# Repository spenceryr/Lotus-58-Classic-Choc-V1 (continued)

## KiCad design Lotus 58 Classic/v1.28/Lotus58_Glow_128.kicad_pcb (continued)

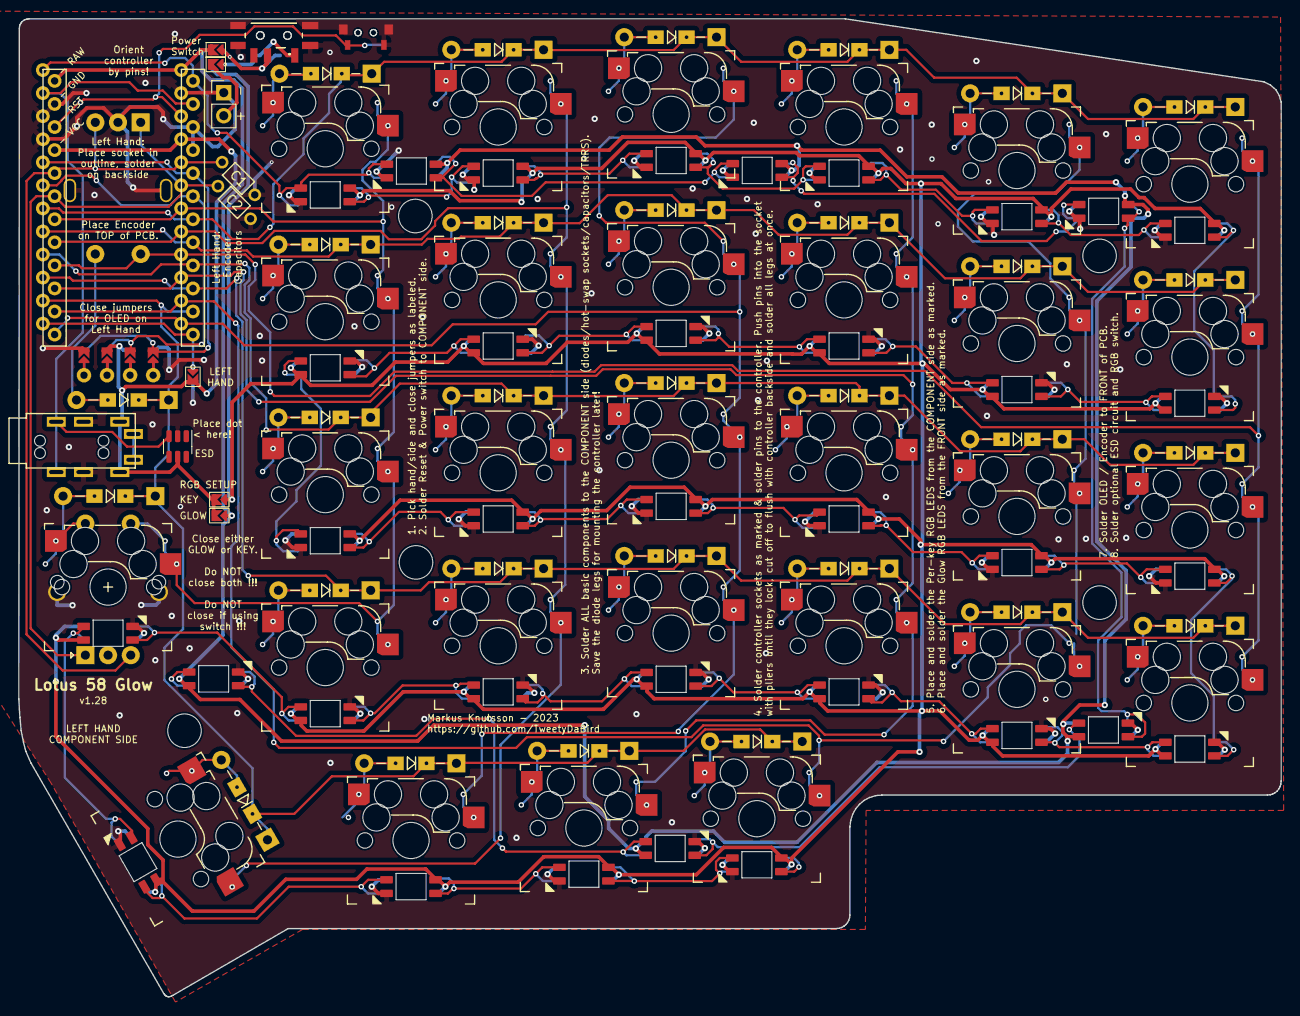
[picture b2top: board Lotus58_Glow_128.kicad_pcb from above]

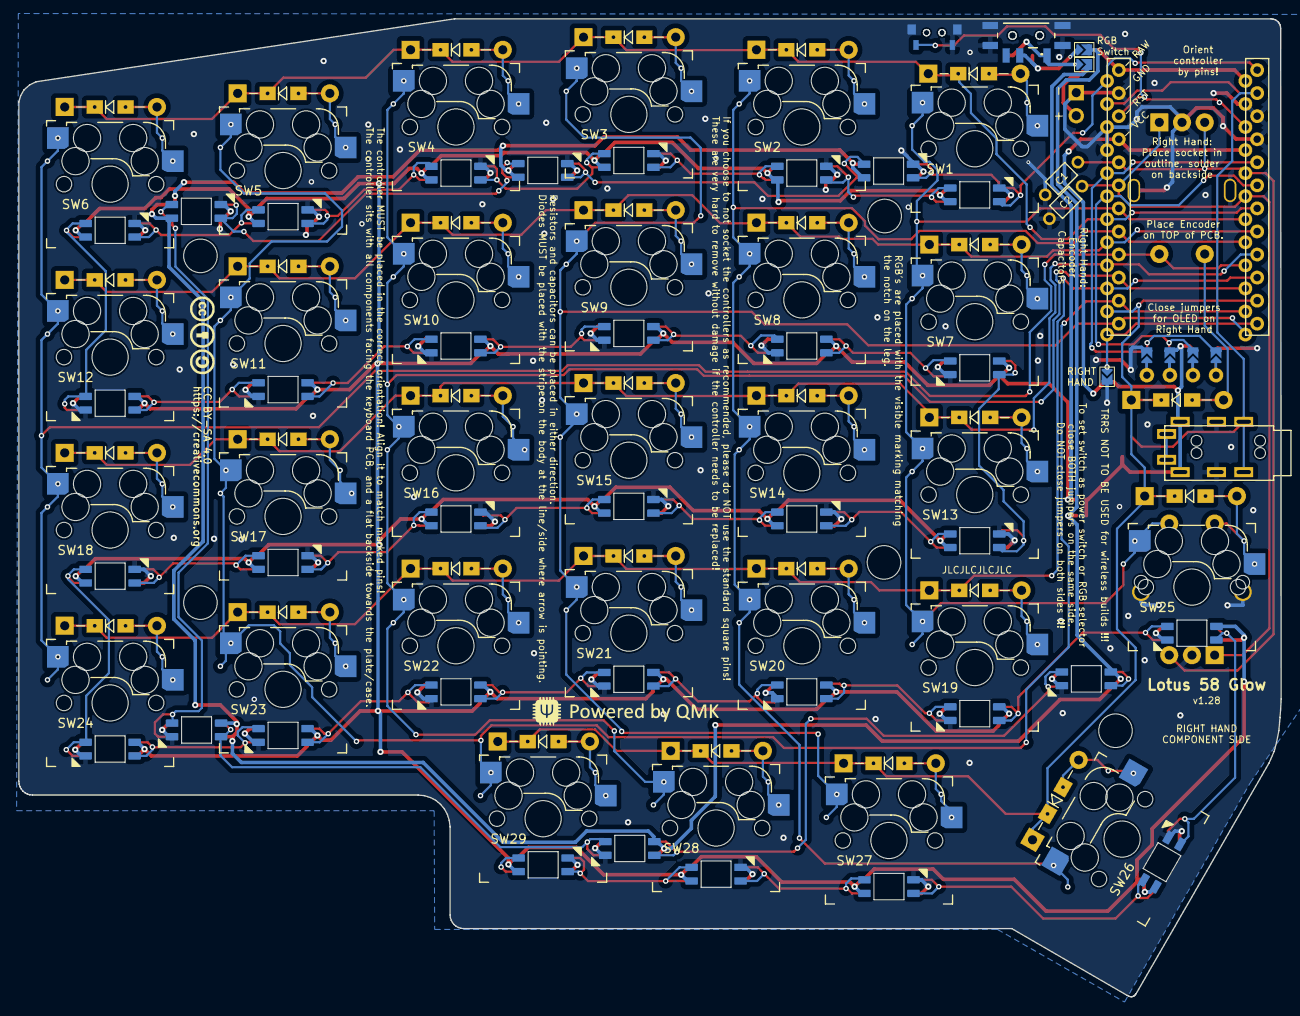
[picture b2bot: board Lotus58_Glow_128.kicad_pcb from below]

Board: 2 copper layers, 139.1 x 107.7 mm, 122 parts (73 on the bottom side), 90 nets.

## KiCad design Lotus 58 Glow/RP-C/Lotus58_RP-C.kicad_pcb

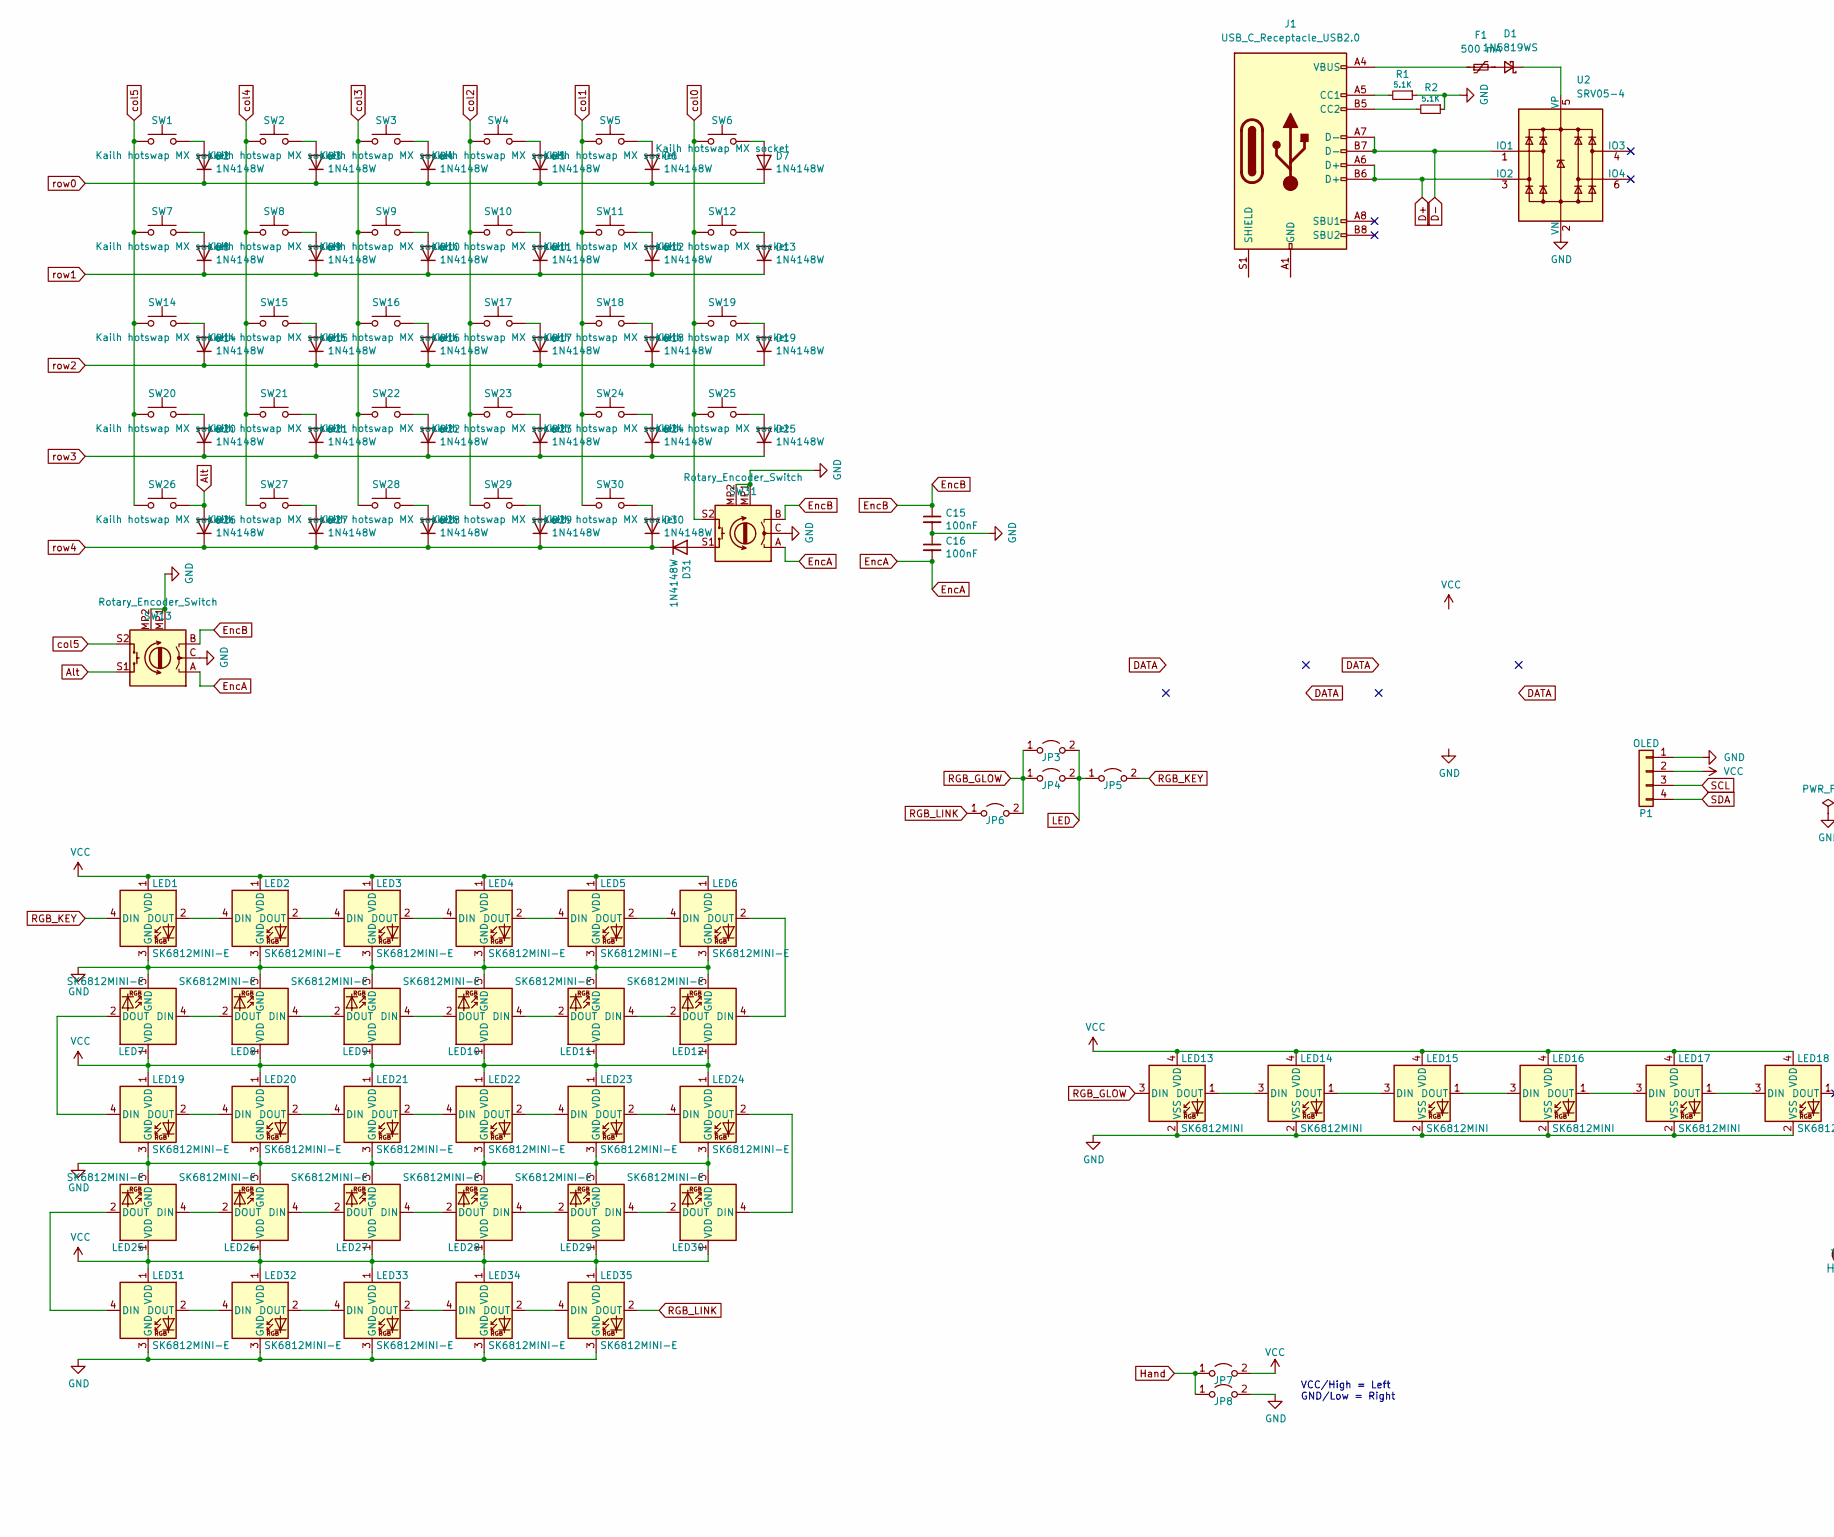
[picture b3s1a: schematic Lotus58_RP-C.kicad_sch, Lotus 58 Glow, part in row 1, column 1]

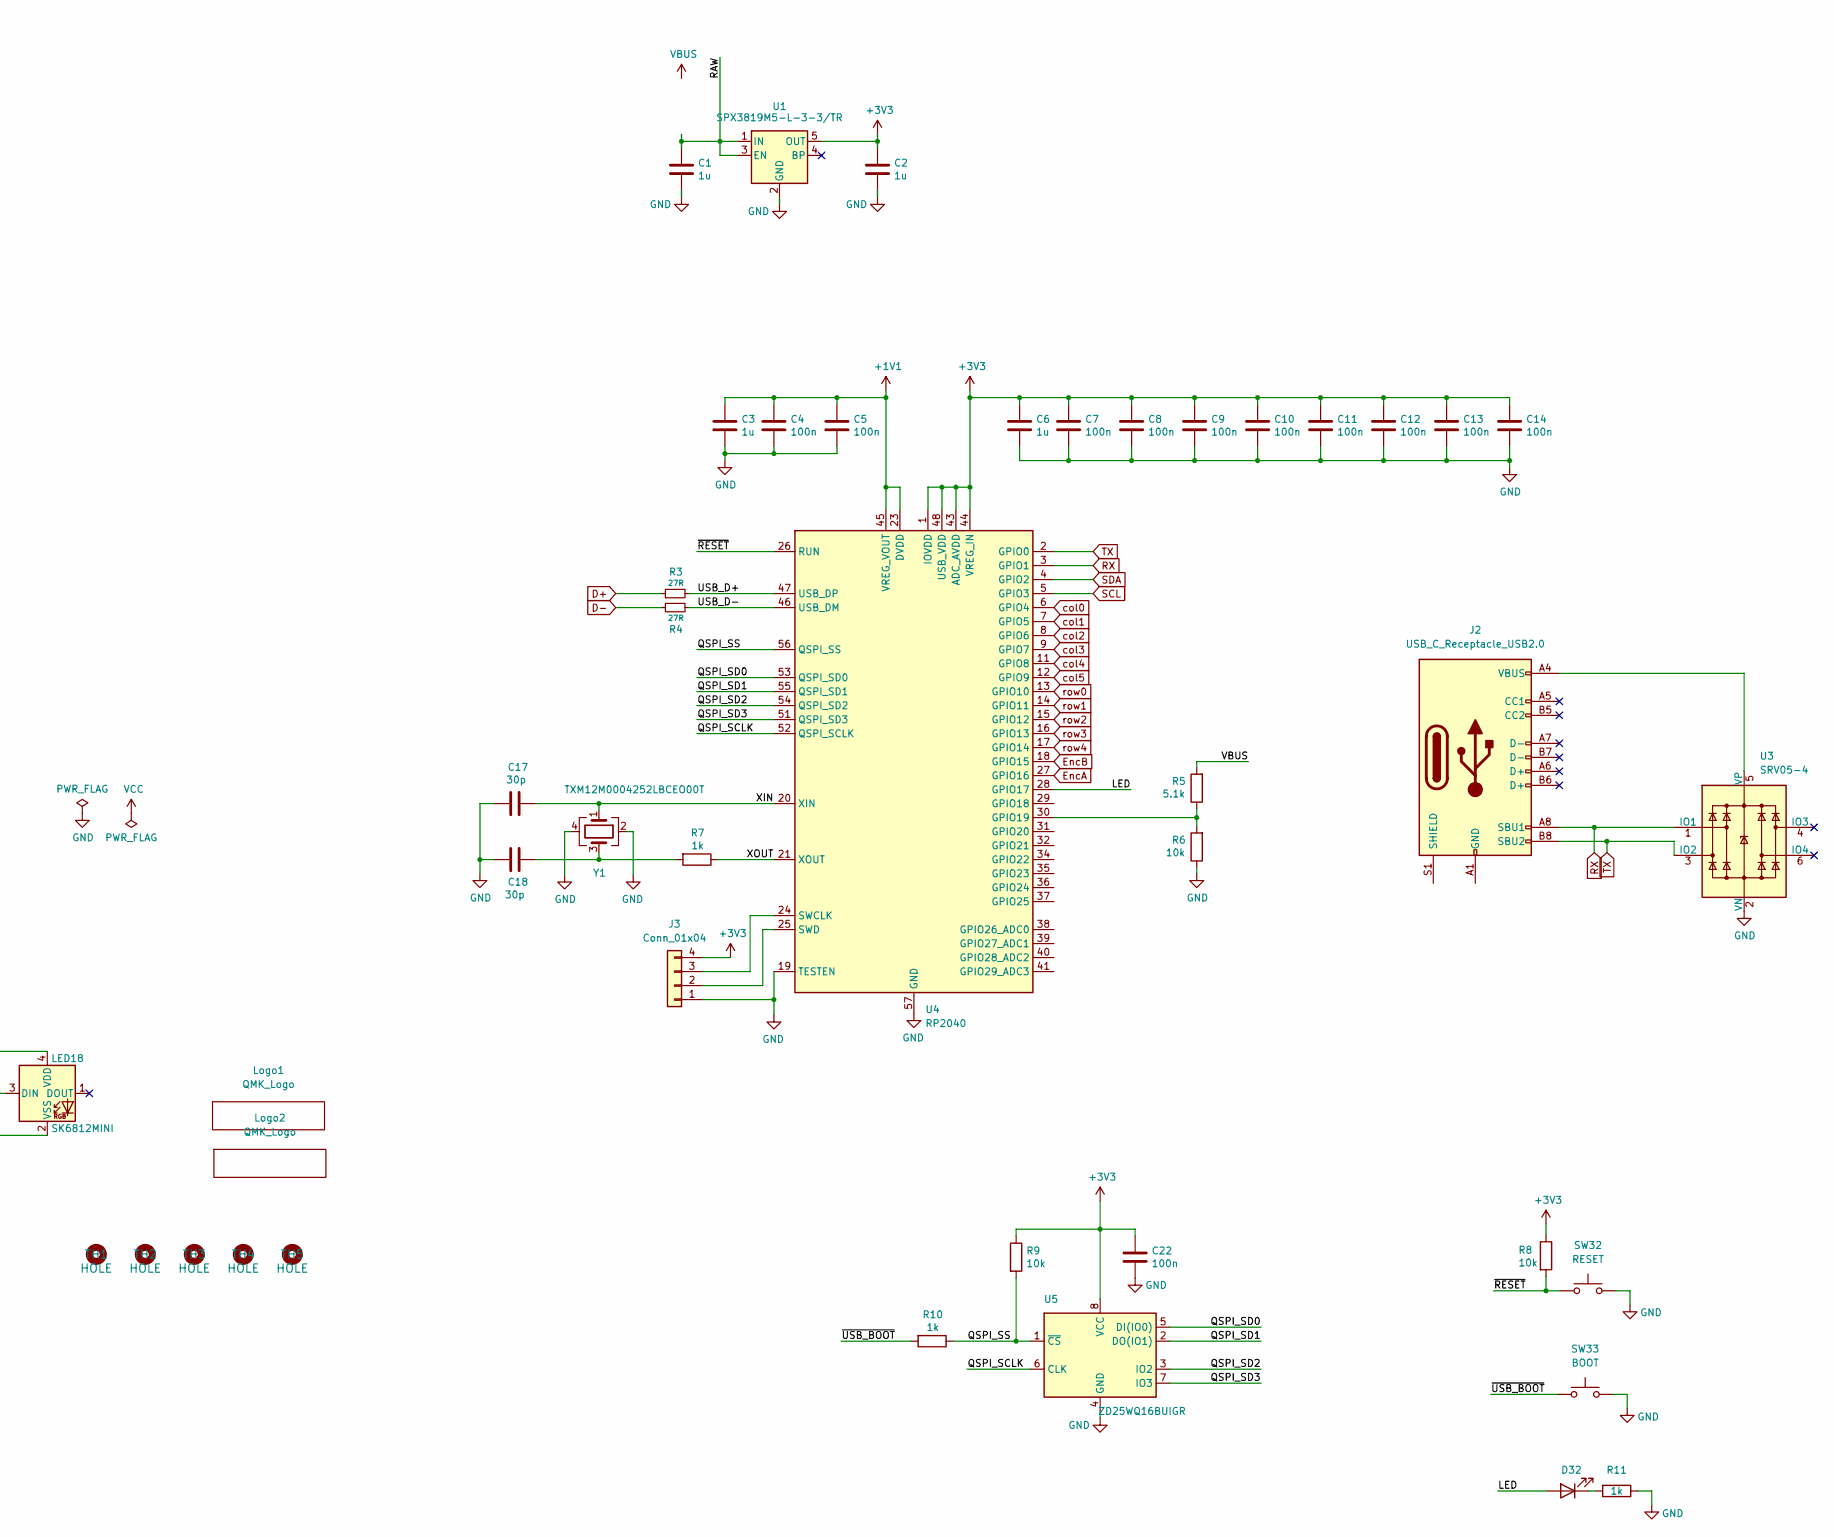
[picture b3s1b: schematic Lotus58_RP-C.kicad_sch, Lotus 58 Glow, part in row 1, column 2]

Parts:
C1, C2, C3, C6: 1u; C_0402_1005Metric
C4, C5, C7, C8, C9, C10, C11, C12, C13, C14, C22: 100n; C_0402_1005Metric
C15, C16: 100nF; RESISTOR_Reversible
C17, C18: 30p; C_0402_1005Metric
D1: 1N5819WS; D_SOD-323F
D2, D3, D4, D5, D6, D7, D8, D9, D10, D11, D12, D13, D14, D15, D16, D17, D18, D19, D20, D21, D22, D23, D24, D25, D26, D27, D28, D29, D30, D31: 1N4148W; D_SOD-123
D32: LED; LED_0402_1005Metric; LCSC C130719
F1: 500 mA; R_0805_2012Metric
J1, J2: USB_C_Receptacle_USB2.0; GT-USB-7014C
J3: Conn_01x04; PinHeader_1x04_P2.00mm_Vertical
JP3, JP4, JP5, JP6: FULL; Jumper_Mini
JP7: LEFT; Jumper_Mini
JP8: RIGHT; Jumper_Mini
LED1, LED2, LED3, LED4, LED5, LED6, LED7, LED8, LED9, LED10, LED11, LED12, LED19, LED20, LED21, LED22, LED23, LED24, LED25, LED26, LED27, LED28, LED29, LED30, LED31, LED32, LED33, LED34, LED35: SK6812MINI-E; MX_SK6812MINI-E_REVERSIBLE
LED13, LED14, LED15, LED16, LED17, LED18: SK6812MINI; LED_SK6812MINI_PLCC4_3.5x3.5mm_P1.75mmdouble
Logo1, Logo2: QMK_Logo; qmk logo
P1: OLED; SSD1306-0.91-OLED-4pin-128x32 doublesided
R1, R2: 5.1K; R_0402_1005Metric
R3, R4: 27R; R_0402_1005Metric
R5: 5.1k; R_0402_1005Metric
R6, R8, R9: 10k; R_0402_1005Metric
R7, R10: 1k; R_0402_1005Metric
R11: 1k; R_0402_1005Metric; LCSC C11702
SW1, SW2, SW3, SW4, SW5, SW6, SW7, SW8, SW9, SW10, SW11, SW12, SW14, SW15, SW16, SW17, SW18, SW19, SW20, SW21, SW22, SW23, SW24, SW25, SW26, SW27, SW28, SW29, SW30: Kailh hotswap MX socket; SW_MX_HotSwap_Reversible
SW13: Rotary_Encoder_Switch; Encoder_Alps_EC11E_Offset_pad
SW31: Rotary_Encoder_Switch; Encoder_Alps_EC11E_Small
SW32: RESET; YTS-A002
SW33: BOOT; YTS-A002
TH1, TH2, TH3, TH4, TH5: HOLE; Spacer PCB hole
U1: SPX3819M5-L-3-3/TR; SOT-23-5
U2, U3: SRV05-4; SOT-23-6; LCSC C558418
U4: RP2040; QFN-56-1EP_7x7mm_P0.4mm_EP3.2x3.2mm
U5: ZD25WQ16BUIGR; DFN-8-1EP_3x2mm_P0.5mm_EP0.2x1.6mm; LCSC C2759920
Y1: TXM12M0004252LBCEO00T; Crystal_SMD_2520-4Pin_2.5x2.0mm; PartNo C284156

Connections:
+1V1: C3.1, C4.1, C5.1, U4.23 (DVDD), U4.45 (VREG_VOUT), U4.50 (DVDD)
+3V3: C2.1, C6.1, C7.1, C8.1, C9.1, C10.1, C11.1, C12.1, C13.1, C14.1, C22.1, J3.4, R8.1, R9.1, U1.5 (OUT), U4.1 (IOVDD), U4.10 (IOVDD), U4.22 (IOVDD), U4.33 (IOVDD), U4.42 (IOVDD), U4.43 (ADC_AVDD), U4.44 (VREG_IN), U4.48 (USB_VDD), U4.49 (IOVDD), U5.8 (VCC)
/QSPI_SCLK: U4.52 (QSPI_SCLK), U5.6 (CLK)
/QSPI_SD0: U4.53 (QSPI_SD0), U5.5 (DI(IO0))
/QSPI_SD1: U4.55 (QSPI_SD1), U5.2 (DO(IO1))
/QSPI_SD2: U4.54 (QSPI_SD2), U5.3 (IO2)
/QSPI_SD3: U4.51 (QSPI_SD3), U5.7 (IO3)
/QSPI_SS: R9.2, R10.1, U4.56 (QSPI_SS), U5.1 (~CS)
/RAW: C1.1, U1.1 (IN), U1.3 (EN)
/USB_D+: R3.2, U4.47 (USB_DP)
/USB_D-: R4.2, U4.46 (USB_DM)
/XIN: C17.1, U4.20 (XIN), Y1.1
/XOUT: R7.1, U4.21 (XOUT)
/~RESET: R8.2, SW32.1, U4.26 (RUN)
/~USB_BOOT: R10.2, SW33.1
Alt: D26.2 (A), SW13.S1, SW26.2
D+: J1.A6 (D+), J1.B6 (D+), R3.1, U2.3 (IO2)
D-: J1.A7 (D-), J1.B7 (D-), R4.1, U2.1 (IO1)
EncA: C16.2, SW13.A, SW31.A, U4.27 (GPIO16)
EncB: C15.1, SW13.B, SW31.B, U4.18 (GPIO15)
GND: C1.2, C2.2, C3.2, C4.2, C5.2, C6.2, C7.2, C8.2, C9.2, C10.2, C11.2, C12.2, C13.2, C14.2, C15.2, C16.1, C17.2, C18.2, C22.2, J3.1, JP8.2 (B), LED1.3 (GND), LED2.3 (GND), LED3.3 (GND), LED4.3 (GND), LED5.3 (GND), LED6.3 (GND), LED7.3 (GND), LED8.3 (GND), LED9.3 (GND), LED10.3 (GND), LED11.3 (GND), LED12.3 (GND), LED13.2 (VSS), LED14.2 (VSS), LED15.2 (VSS), LED16.2 (VSS), LED17.2 (VSS), LED18.2 (VSS), LED19.3 (GND), LED20.3 (GND), LED21.3 (GND), LED22.3 (GND), LED23.3 (GND), LED24.3 (GND), LED25.3 (GND), LED26.3 (GND), LED27.3 (GND), LED28.3 (GND), LED29.3 (GND), LED30.3 (GND), LED31.3 (GND), LED32.3 (GND), LED33.3 (GND), LED34.3 (GND), LED35.3 (GND), P1.1, R1.1, R2.1, R6.1, R11.1, SW13.C, SW13.MP1 (GND), SW13.MP2 (GND), SW31.C, SW31.MP1 (GND), SW31.MP2 (GND), SW32.2, SW33.2, U1.2 (GND), U2.2 (VN), U3.2 (VN), U4.19 (TESTEN), U4.57 (GND), U5.4 (GND), Y1.2, Y1.4
Hand: JP7.1 (A), JP8.1 (A)
LED: D32.2 (A), JP3.2 (B), JP4.2 (B), JP5.1 (A), U4.28 (GPIO17)
unnamed: C18.1, R7.2, Y1.3
unnamed: D1.1 (K), U2.5 (VP)
unnamed: D1.2 (A), F1.2
unnamed: D2.2 (A), SW1.1
unnamed: D3.2 (A), SW2.1
unnamed: D4.2 (A), SW3.1
unnamed: D5.2 (A), SW4.1
unnamed: D6.2 (A), SW5.1
unnamed: D7.2 (A), SW6.1
unnamed: D8.2 (A), SW7.1
unnamed: D9.2 (A), SW8.1
unnamed: D10.2 (A), SW9.1
unnamed: D11.2 (A), SW10.1
unnamed: D12.2 (A), SW11.1
unnamed: D13.2 (A), SW12.1
unnamed: D14.2 (A), SW14.1
unnamed: D15.2 (A), SW15.1
unnamed: D16.2 (A), SW16.1
unnamed: D17.2 (A), SW17.1
unnamed: D18.2 (A), SW18.1
unnamed: D19.2 (A), SW19.1
unnamed: D20.2 (A), SW20.1
unnamed: D21.2 (A), SW21.1
unnamed: D22.2 (A), SW22.1
unnamed: D23.2 (A), SW23.1
unnamed: D24.2 (A), SW24.1
unnamed: D25.2 (A), SW25.1
unnamed: D27.2 (A), SW27.1
unnamed: D28.2 (A), SW28.1
unnamed: D29.2 (A), SW29.1
unnamed: D30.2 (A), SW30.1
unnamed: D31.2 (A), SW31.S1
unnamed: D32.1 (K), R11.2
unnamed: F1.1, J1.A4 (VBUS), J1.A9 (VBUS), J1.B4 (VBUS), J1.B9 (VBUS)
unnamed: J1.A1 (GND), J1.A12 (GND), J1.B1 (GND), J1.B12 (GND)
unnamed: J1.A5 (CC1), R1.2
unnamed: J1.B5 (CC2), R2.2
unnamed: J2.A1 (GND), J2.A12 (GND), J2.B1 (GND), J2.B12 (GND)
unnamed: J2.A4 (VBUS), J2.A9 (VBUS), J2.B4 (VBUS), J2.B9 (VBUS), U3.5 (VP)
unnamed: J3.2, U4.25 (SWD)
unnamed: J3.3, U4.24 (SWCLK)
unnamed: LED1.2 (DOUT), LED2.4 (DIN)
unnamed: LED2.2 (DOUT), LED3.4 (DIN)
unnamed: LED3.2 (DOUT), LED4.4 (DIN)
unnamed: LED4.2 (DOUT), LED5.4 (DIN)
unnamed: LED5.2 (DOUT), LED6.4 (DIN)
unnamed: LED7.4 (DIN), LED8.2 (DOUT)
unnamed: LED8.4 (DIN), LED9.2 (DOUT)
unnamed: LED9.4 (DIN), LED10.2 (DOUT)
unnamed: LED10.4 (DIN), LED11.2 (DOUT)
unnamed: LED11.4 (DIN), LED12.2 (DOUT)
unnamed: LED6.2 (DOUT), LED12.4 (DIN)
unnamed: LED13.1 (DOUT), LED14.3 (DIN)
unnamed: LED14.1 (DOUT), LED15.3 (DIN)
unnamed: LED15.1 (DOUT), LED16.3 (DIN)
unnamed: LED16.1 (DOUT), LED17.3 (DIN)
unnamed: LED17.1 (DOUT), LED18.3 (DIN)
unnamed: LED19.2 (DOUT), LED20.4 (DIN)
unnamed: LED7.2 (DOUT), LED19.4 (DIN)
unnamed: LED20.2 (DOUT), LED21.4 (DIN)
unnamed: LED21.2 (DOUT), LED22.4 (DIN)
unnamed: LED22.2 (DOUT), LED23.4 (DIN)
unnamed: LED23.2 (DOUT), LED24.4 (DIN)
unnamed: LED24.2 (DOUT), LED30.4 (DIN)
unnamed: LED25.2 (DOUT), LED31.4 (DIN)
unnamed: LED25.4 (DIN), LED26.2 (DOUT)
unnamed: LED26.4 (DIN), LED27.2 (DOUT)
unnamed: LED27.4 (DIN), LED28.2 (DOUT)
unnamed: LED28.4 (DIN), LED29.2 (DOUT)
unnamed: LED29.4 (DIN), LED30.2 (DOUT)
unnamed: LED31.2 (DOUT), LED32.4 (DIN)
unnamed: LED32.2 (DOUT), LED33.4 (DIN)
unnamed: LED33.2 (DOUT), LED34.4 (DIN)
unnamed: LED34.2 (DOUT), LED35.4 (DIN)
unnamed: R5.1, R6.2, U4.30 (GPIO19)
RGB_GLOW: JP3.1 (A), JP4.1 (A), JP6.2 (B), LED13.3 (DIN)
RGB_KEY: JP5.2 (B), LED1.4 (DIN)
RGB_LINK: JP6.1 (A), LED35.2 (DOUT)
RX: J2.A8 (SBU1), U3.1 (IO1), U4.3 (GPIO1)
SCL: P1.3, U4.5 (GPIO3)
SDA: P1.4, U4.4 (GPIO2)
TX: J2.B8 (SBU2), U3.3 (IO2), U4.2 (GPIO0)
VBUS: R5.2
VCC: JP7.2 (B), LED1.1 (VDD), LED2.1 (VDD), LED3.1 (VDD), LED4.1 (VDD), LED5.1 (VDD), LED6.1 (VDD), LED7.1 (VDD), LED8.1 (VDD), LED9.1 (VDD), LED10.1 (VDD), LED11.1 (VDD), LED12.1 (VDD), LED13.4 (VDD), LED14.4 (VDD), LED15.4 (VDD), LED16.4 (VDD), LED17.4 (VDD), LED18.4 (VDD), LED19.1 (VDD), LED20.1 (VDD), LED21.1 (VDD), LED22.1 (VDD), LED23.1 (VDD), LED24.1 (VDD), LED25.1 (VDD), LED26.1 (VDD), LED27.1 (VDD), LED28.1 (VDD), LED29.1 (VDD), LED30.1 (VDD), LED31.1 (VDD), LED32.1 (VDD), LED33.1 (VDD), LED34.1 (VDD), LED35.1 (VDD), P1.2
col0: SW6.2, SW12.2, SW19.2, SW25.2, SW31.S2, U4.6 (GPIO4)
col1: SW5.2, SW11.2, SW18.2, SW24.2, SW30.2, U4.7 (GPIO5)
col2: SW4.2, SW10.2, SW17.2, SW23.2, SW29.2, U4.8 (GPIO6)
col3: SW3.2, SW9.2, SW16.2, SW22.2, SW28.2, U4.9 (GPIO7)
col4: SW2.2, SW8.2, SW15.2, SW21.2, SW27.2, U4.11 (GPIO8)
col5: SW1.2, SW7.2, SW13.S2, SW14.2, SW20.2, SW26.1, U4.12 (GPIO9)
row0: D2.1 (K), D3.1 (K), D4.1 (K), D5.1 (K), D6.1 (K), D7.1 (K), U4.13 (GPIO10)
row1: D8.1 (K), D9.1 (K), D10.1 (K), D11.1 (K), D12.1 (K), D13.1 (K), U4.14 (GPIO11)
row2: D14.1 (K), D15.1 (K), D16.1 (K), D17.1 (K), D18.1 (K), D19.1 (K), U4.15 (GPIO12)
row3: D20.1 (K), D21.1 (K), D22.1 (K), D23.1 (K), D24.1 (K), D25.1 (K), U4.16 (GPIO13)
row4: D26.1 (K), D27.1 (K), D28.1 (K), D29.1 (K), D30.1 (K), D31.1 (K), U4.17 (GPIO14)

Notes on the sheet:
VCC/High = Left GND/Low = Right

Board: 2 copper layers, 154 parts (33 on the bottom side), 117 nets, no tracks yet.

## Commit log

2022-03-24 Housekeeping
2022-03-24 Added compiled firmware examples
2022-04-26 Added pdf
2022-04-26 Added Firmware
2022-06-01 Prep for merge
2022-06-02 v1.24 prototype
2022-06-10 Added viewable schematic
2022-09-14 v1.24
    Tweaks to silkscreen, reworked RGB jumpers.
2022-09-14 backup
2022-09-25 quick typo fix in the README for JLCPCB
2022-10-11 updated firmware
2022-10-13 v1.24 updates
    Moved OLED 1 mm down
    Added footprint for SRV05-04 ESD protection on TRRS
    Silkscreen improvements
2022-10-19 Firmware update
    Added nanoBoot
2022-10-19 Firmware added
    Added Production Firmware
2022-10-24 Moving v1.24 to testing
2022-10-24 Trying USB C
2022-10-25 Lotus 58 C v1.0.0
    Moved to full SMD and USB-C
2022-10-25 Lotus C
    Minor tweaks
    SMD capacitors
2022-10-25 Glow v1.24
    Final tweaks
2022-10-25 Remove left over prototype files
2022-10-25 cleanup
2022-10-25 merge
2022-10-25 Renamed folders
2022-10-25 Readme for Glow
2022-10-25 removed orig files
2022-10-25 retrieved old
2022-10-25 Removed folder
2022-11-02 Adding Lotus WL
2022-11-11 Minor tweaks
2022-11-23 v1.24 tweaks
2022-11-23 General cleanup and rename
2022-11-29 silkscreen update v1.2.4
2022-12-09 v1.2.4
    Ordered prototype
2023-02-16 Update README.md
    Clarified boot-loader flashing.
2023-02-16 Update README.md
    Fixed spelling.
2023-02-16 Update README.md
    Fixed more spelling.
2023-02-16 Update README.md
    Added QMK blurb.
2023-02-16 Added Atmel-DFU
    Added Atmel-DFU pre-compiled firmware
2023-02-18 Updated Firmware
    Corrected encoder index
2023-02-25 created wireless
2023-04-25 reorganizing firmware
2023-04-25 Write down nanoBoot burning guide - These are the instructions I followed to burn nanoBoot without a spare Pro Micro
2023-04-29 rename file
2023-04-29 renamed bootloader
2023-05-26 Revert "Delete Lotus 58 Glow/v1.25 directory"
    This reverts commit 31d979d12f78d2f2b7a7d2bcfd21e5f2126dafa7.
2023-05-26 v1.2.5
    Redesign of ProMicro socket
2023-05-26 Created rp2040 variant
2023-06-09 v1.3.0 initial
    New version with USB C and a centered controller footprint
2023-06-09 Revert "Merge branch 'development' into prototype"
    This reverts commit 35509e389ef8b26fb35347eea18a2192f52b11e9.
2023-07-26 Added 1.3.1
    minor corrections on jumper pads
2023-08-06 Regenerated DXF files
    Keep in mind, there is no tool kerf in these files, so that will need to be added as per your manufacturers choice
2023-08-21 minor tweak
2023-08-26 Version 1.32
    Tweaks, and RGB rework
2023-08-26 Renamed folder to Classic/USB-C
2023-08-26 Housekeeping after merge
2023-08-26 Fixed Readme
2023-08-26 v1.32
    Minor concessions for 3D printing
2023-08-26 v1.31 removed
    Superseededed by 1.32
2023-08-26 v1.32 superseedes 1.31
2023-08-29 v1.33 superseedes 1.31
    Minor fixes to make 3D printing easier
2023-08-30 v1.26 initial
2023-08-30 v1.26 final
2023-09-12 Updated plates
    Plates now have no copper layer, both preparing for wireless, and to avoid scratches/shorting, if OLED etc. is not soldered with flat pads.
2023-09-12 Updated Plates
    Prep for wireless, removing copper fill.
2023-09-12 Repair bootloader folder
2023-09-12 v1.30 to released
2023-09-13 Corrected filename for v1.33 files
2023-09-13 v1.26 Release
    Stupid Git
2023-09-13 Revert "Merge pull request #53 from TweetyDaBird/release"
    This reverts commit d5395b9879702c31b6de7b44cd45c4487da02165, reversing
    changes made to 721366541e1b3daa08e8a27e832954bcb38f5212.
    # Conflicts:
    # .gitignore
    # Lotus 58 Classic/v1.26/Lotus58_Glow_126.kicad_pcb
2023-09-13 Fixing my mistakes...
2023-10-14 Fixed silk screen inconsistencies
2023-10-14 testing wireless
2023-11-22 Lotus 58 USB-C v1.40
    Initial commit
2023-11-22 Lotus 58 Classic v1.27
    Initial commit
2023-11-22 Revert "Lotus 58 Classic v1.27"
    This reverts commit 127257085023c495304368bac738313ddacfc2f8.
2023-11-22 L58 C v1.40
    fix silkscreen
2023-12-16 Created STEP files for 3D model
2023-12-27 tweak v1.28
2023-12-27 Initial commit v1.28
2023-12-27 Removing unsuitable relaeases
2024-02-07 v1.41 tweaks
2024-03-23 Added Readme v1.41
2024-11-24 Initial changes for kailh choc V1 hostswaps
    * Changed footprint for switches to kailh choc V1 hotswaps
    * Change per-key and underglow LED positions
    * Rerouted all tracks for LEDS and switches
    * Removed encoder near thumb cluster
2024-11-25 Add voltage translator for LEDs with RP2040
    * Added voltage translator
    - Routed USB Raw 5V from controller board to LED translator for use by
    LEDs
    * Rerouted power link between boards to use USB Raw 5V instead of
    controller VCC
    * Added additional backside placement for components
2024-11-28 Small project changes
2024-12-05 Added decoupling capacitors for level shifter
    * Also changed encoder decoupling capacitors to SMD components
2025-01-07 Small trace changes to appease JLCDFM
2025-02-03 Add bottom tray case for right side
2025-07-09 Increase height of tray case by 1mm
    Also added left hand side tray case, which is just the right
    side tray case flipped.
2025-07-09 Add plate files
